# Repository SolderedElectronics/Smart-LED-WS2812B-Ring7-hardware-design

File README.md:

# Smart LED WS2812B Ring7 Hardware Design

## About the Product

|  |
| :----------------------------------------------------------: |
| [Buy Smart LED WS2812B Ring7](https://www.solde.red/333055) |

WS2812B is an extremely interesting LED that can emit light in red, green or blue – or any combination of these three colors, able to show a total of approximately 16 million different colors. On this board, diodes are arranged in a circle. They are controlled by a single pin with only a few lines of code from Arduino IDE. That’s possible thanks to the integrated controller inside the LED itself!

---

## Repository Contents

This repository contains all design files for Smart LED WS2812B Ring7, organized as follows:

- **`CAD` folder**: Contains KiCAD design files, including:
  - Schematics
  - PCB layout
  - Panel PCB layout
  - Source 3D files in Fusion360, if any
  - All files are sorted by version with a detailed change log.
- **`OUTPUTS` folder**: Includes all production-ready files, such as:
  - Bill of Materials (BOM) and interactive BOM (iBOM)
  - PDF versions of schematics
  - 3D `.step` file of the board
  - 3D-printable models
  - Gerber files for PCB manufacturing
  - Image of the pinout of the board
  - Product image
  - Compliance, legal and generic sales documents

Refer to the `Change Log` in the CAD folder for details about updates between versions.

---

## Learn More About the Product

Beyond the repository, explore the following resources:

### Soldered Verify

The **Soldered Verify** system ensures every board you purchase from Soldered is fully functional. It also provides access to exclusive test data for your product. To get started, find the unique Soldered Verify ID on your product's packaging and enter the ID on the [Soldered Verify page](https://soldered.com/verify/) to access test results and additional product details.

### Soldered Community

Soldered Community is your go-to place for technical support. Our engineers track and answer all questions posted there, and it’s a great space for the maker community. Get answers to your questions and solutions for your challenges at [Soldered Community](https://soldered.com/community).

### solde.red

solde.red is an ultimate URL shortener and information hub. Access it by typing solde.red/ followed by your product SKU, e.g., [solde.red/333000](https://solde.red/333000), to find getting-started guides, datasheets, open-source hardware and software files, certifications, images, pinouts, and more. Read more about the shortener [here](https://solde.red/info/).

---

## Contributing

Contributions are welcome! Here’s how you can get involved:

- Submit pull requests to enhance the design or fix issues.
- Report bugs or problems by opening an issue.

We encourage community collaboration to make this product even better.

---

## About Soldered

[Soldered for Makers](https://soldered.com) specializes in designing and manufacturing electronic products tailored for enthusiasts, ranging from hobbyists to professionals. Our portfolio includes electronic boards, sensors, and actuators that are widely utilized in fields such as microelectronics, mechatronics, robotics, programming, and IoT. Every product we offer is designed in-house and built upon open-source hardware and software platforms. Proudly certified and manufactured within the European Union, our catalog likely includes the product you need for your project.

We complement these products with comprehensive tutorials and manuals, product descriptions, schematics, programming codes, and project examples. Our round-the-clock [customer and technical support](https://soldered.com/community) is available for all our products, irrespective of the sales channel. Soldered’s success and services reflect our maker community’s unwavering [trust](https://www.trustpilot.com/review/soldered.com), for which we are deeply grateful. Join our community and create using Soldered products.

---

## License

All Soldered open-source hardware (OSH) is under The TAPR Open Hardware License. Read more in the LICENSE file located in this repository.

**Disclaimer:**

No warranty - all designs in this repository are distributed in the hope that they will be useful, but without any warranty. They are provided "AS IS", therefore without warranty of any kind, either expressed or implied. The entire quality and performance of what you do with the contents of this repository are your responsibility. In no event Soldered Electronics will be liable for your damages, or losses, including any general, special, incidental, or consequential damage arising out of the use or inability to use the contents of this repository. 

---

## Have fun!

Thank you for your support from your fellow makers at Soldered Electronics.

Happy Making!

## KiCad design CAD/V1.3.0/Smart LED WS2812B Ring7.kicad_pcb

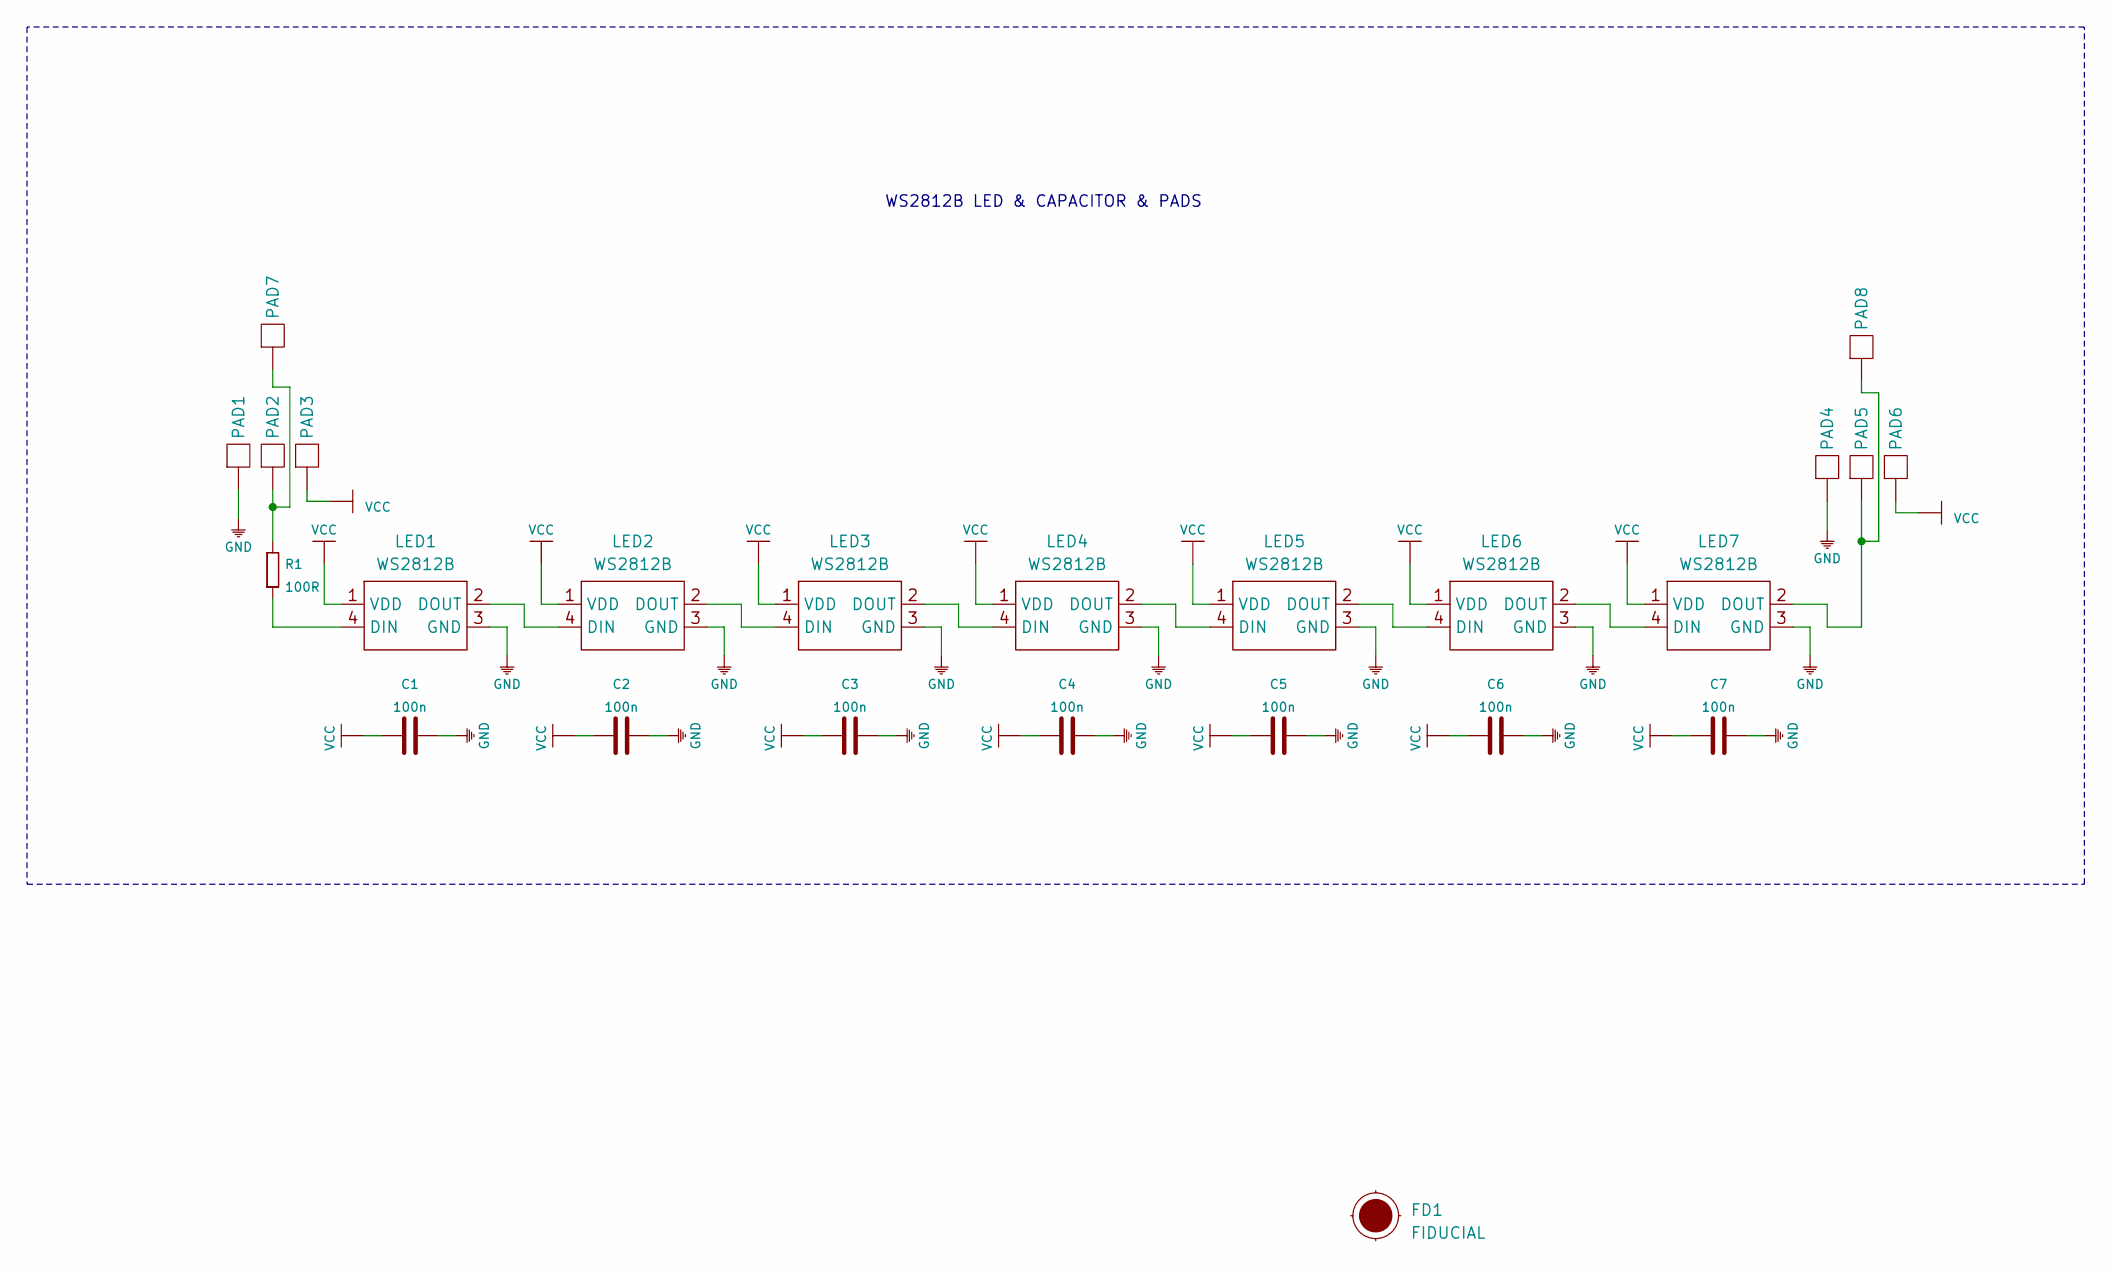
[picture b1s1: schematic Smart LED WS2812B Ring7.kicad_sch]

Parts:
C1, C2, C3, C4, C5, C6, C7: 100n; 0603C
FD1: FIDUCIAL; FIDUCIAL_23
LED1, LED2, LED3, LED4, LED5, LED6, LED7: WS2812B; WS2812B LED
PAD1, PAD2, PAD3, PAD4, PAD5, PAD6, PAD7, PAD8: PAD_2x1.5
R1: 100R; 0603R

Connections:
GND: C1.2, C2.2, C3.2, C4.2, C5.2, C6.2, C7.2, LED1.3 (GND), LED2.3 (GND), LED3.3 (GND), LED4.3 (GND), LED5.3 (GND), LED6.3 (GND), LED7.3 (GND), PAD1.1, PAD4.1
unnamed: LED1.2 (DOUT), LED2.4 (DIN)
unnamed: LED1.4 (DIN), R1.1
unnamed: LED2.2 (DOUT), LED3.4 (DIN)
unnamed: LED3.2 (DOUT), LED4.4 (DIN)
unnamed: LED4.2 (DOUT), LED5.4 (DIN)
unnamed: LED5.2 (DOUT), LED6.4 (DIN)
unnamed: LED6.2 (DOUT), LED7.4 (DIN)
unnamed: LED7.2 (DOUT), PAD5.1, PAD8.1
unnamed: PAD2.1, PAD7.1, R1.2
VCC: C1.1, C2.1, C3.1, C4.1, C5.1, C6.1, C7.1, LED1.1 (VDD), LED2.1 (VDD), LED3.1 (VDD), LED4.1 (VDD), LED5.1 (VDD), LED6.1 (VDD), LED7.1 (VDD), PAD3.1, PAD6.1

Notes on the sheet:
WS2812B LED & CAPACITOR & PADS

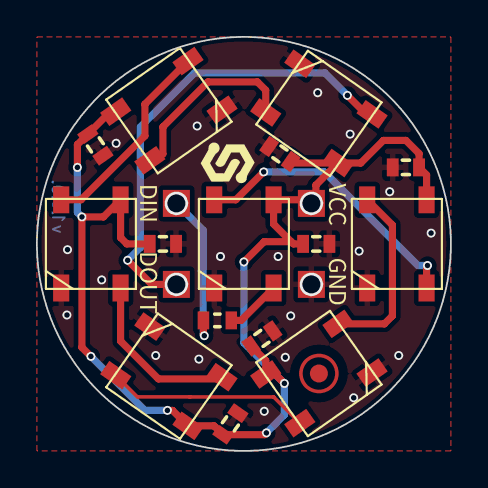
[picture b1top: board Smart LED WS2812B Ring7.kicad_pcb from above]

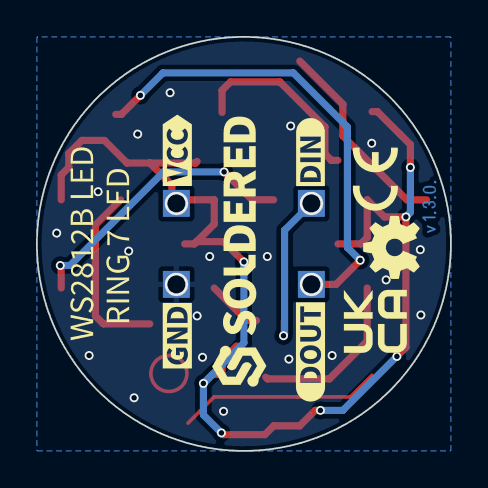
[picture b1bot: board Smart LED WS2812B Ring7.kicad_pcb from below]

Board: 2 copper layers, 23.0 x 23.0 mm, 34 parts (10 on the bottom side), 11 nets.

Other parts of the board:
kibuzzard-651575D0: G***; kibuzzard-651575D0
kibuzzard-651575E0: G***; kibuzzard-651575E0
kibuzzard-651575F3: G***; kibuzzard-651575F3
kibuzzard-651575FD: G***; kibuzzard-651575FD
kibuzzard-6515768A: G***; kibuzzard-6515768A
kibuzzard-65157673: G***; kibuzzard-65157673
kibuzzard-65157800: G***; kibuzzard-65157800
kibuzzard-65157813: G***; kibuzzard-65157813
kibuzzard-65157826: G***; kibuzzard-65157826
kibuzzard-65157840: G***; kibuzzard-65157840

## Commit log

2022-08-06 Updating open source files.
